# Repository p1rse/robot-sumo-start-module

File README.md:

Robot-sumo start module
=====================
Visit http://www.startmodule.com for information of how the start module system works.

This page is mainly for those who are interested in the sourcecode and schematics of the start module.

Purpose
====================
The purpose of this git repository is to maintain the robot-sumo start module system which is an open source and open hardware project.n
The purpose of the module is to make robot-sumo matches more fair and less time consuming by eliminating the possibilites of false starts.
This is done by each robot having a receiver(start module) that are programmed to suply the robot with at start signal when the referee sends the signal via an IR-remote.

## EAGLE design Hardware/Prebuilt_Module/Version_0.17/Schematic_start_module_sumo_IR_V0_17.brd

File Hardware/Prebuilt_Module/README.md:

Read me
=====================

The prebuilt modules are intended to be manufactured in larger quantities with pick and place machinery, this is to reduce size and cost.
The microcontroller on the prebuilt module has a very small amount of flash therefore the code is optimised for size and not so easy to understand.
If you have designed your own hardware and want to create code for this it is better to look at the code in the "Generic" folders.

Harware Version history
=====
Hardware version 0.16 is the version that was first sold at RobotChallenge 2012

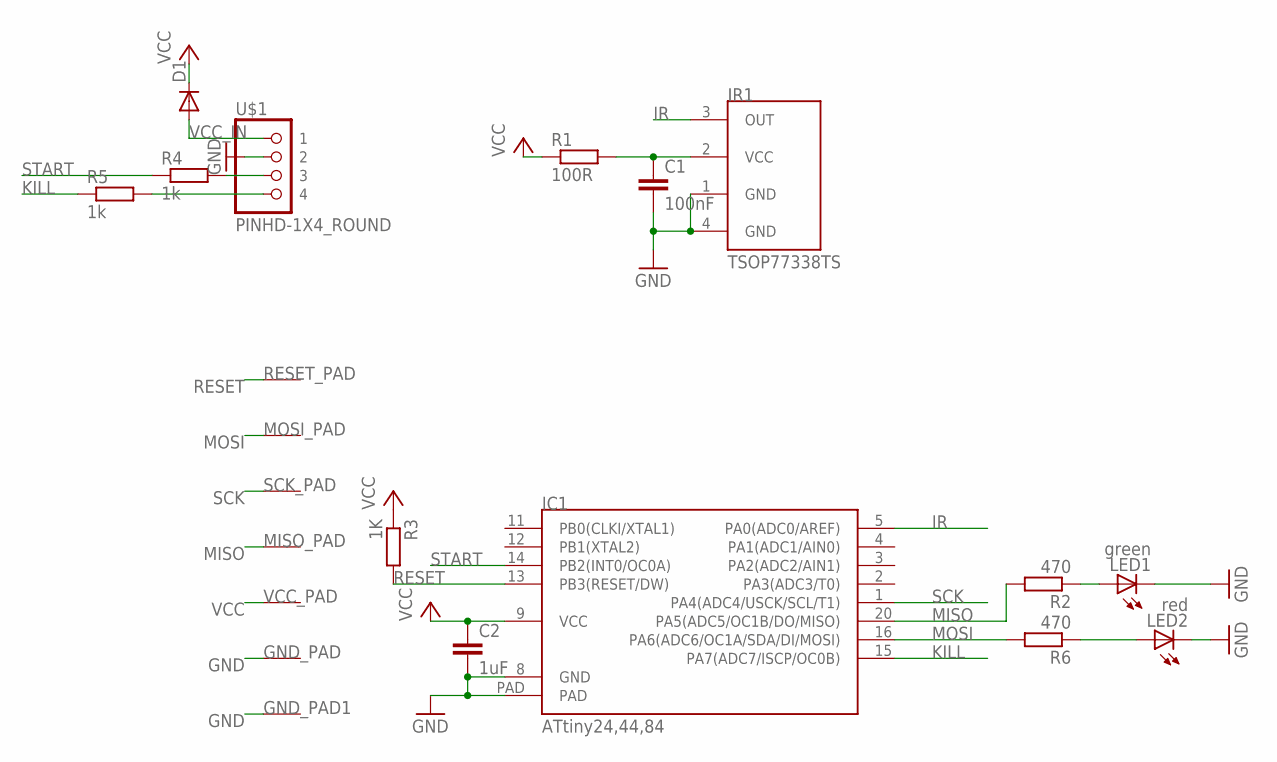
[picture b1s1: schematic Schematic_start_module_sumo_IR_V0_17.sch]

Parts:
C1: 100nF; C0603
C2: 1uF; C0603
D1: DIODE-SOD523; SOD523
GND_PAD: PAD50X50; PAD_50X50
GND_PAD1: PAD75X75; PAD_75X75
IC1: ATTINY24,44,84_QFNVQFN; VQFN20
IR1: TSOP77338TS; TSOP77338
LED1: green; 0603_SMALL
LED2: red; 0603_SMALL
MISO_PAD: PAD50X50; PAD_50X50
MOSI_PAD: PAD50X50; PAD_50X50
R1: 100R; R0402
R2, R6: 470; R0402
R3: 1K; R0402
R4, R5: 1k; R0402
RESET_PAD: PAD50X50; PAD_50X50
SCK_PAD: mosi; PAD_75X75
U$1: PINHD-1X4_ROUND; 1X04_ROUND
VCC_PAD: PAD50X50; PAD_50X50

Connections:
GND: C1.2, C2.2, GND_PAD.P$1, GND_PAD1.P$1, IC1.8 (GND), IC1.PAD, IR1.1 (GND), IR1.4 (GND), LED1.2 (C), LED2.2 (C), U$1.2
IR: IC1.5 (PA0(ADC0/AREF)), IR1.3 (OUT)
KILL: IC1.15 (PA7(ADC7/ISCP/OC0B)), R5.1
MISO: IC1.20 (PA5(ADC5/OC1B/DO/MISO)), MISO_PAD.P$1, R2.2
MOSI: IC1.16 (PA6(ADC6/OC1A/SDA/DI/MOSI)), MOSI_PAD.P$1, R6.2
unnamed: LED2.1 (A), R6.1
unnamed: C1.1, IR1.2 (VCC), R1.2
unnamed: LED1.1 (A), R2.1
unnamed: R5.2, U$1.4
unnamed: R4.2, U$1.3
RESET: IC1.13 (PB3(RESET/DW)), R3.2, RESET_PAD.P$1
SCK: IC1.1 (PA4(ADC4/USCK/SCL/T1)), SCK_PAD.P$1
START: IC1.14 (PB2(INT0/OC0A)), R4.1
VCC: C2.1, D1.C, IC1.9 (VCC), R1.1, R3.1, VCC_PAD.P$1
VCC_IN: D1.A, U$1.1

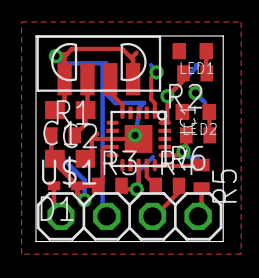
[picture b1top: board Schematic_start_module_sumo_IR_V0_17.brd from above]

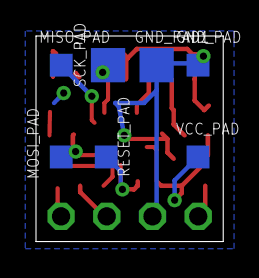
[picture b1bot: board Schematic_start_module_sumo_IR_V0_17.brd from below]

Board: 2 copper layers, 10.4 x 11.4 mm, 21 parts (7 on the bottom side), 15 nets.

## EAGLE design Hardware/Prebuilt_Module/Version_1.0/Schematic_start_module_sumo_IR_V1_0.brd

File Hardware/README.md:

Hardware
====================

Prebuilt_Module - this is the module built with pick and place machines.

Remote_Control - used by referees

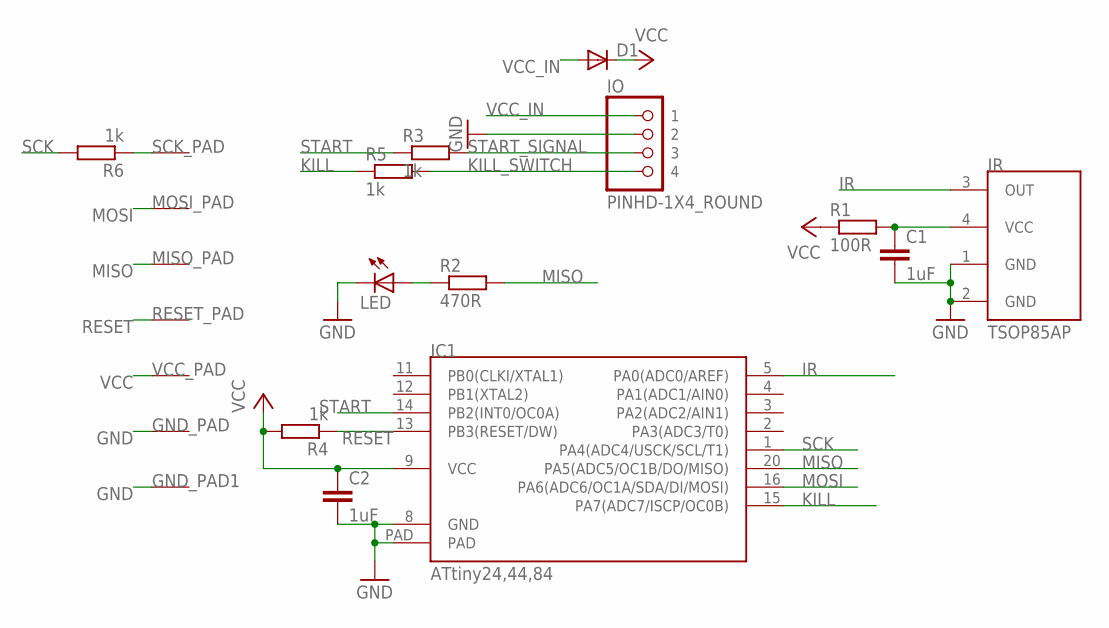
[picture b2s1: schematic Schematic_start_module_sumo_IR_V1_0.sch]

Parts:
C1, C2: 1uF; C0603
D1: DIODE-SOD523; SOD523
GND_PAD: PAD50X50; PAD_50X50
GND_PAD1: PAD75X75; PAD_75X75
IC1: ATTINY24,44,84_QFNVQFN; VQFN20
IO: PINHD-1X4_ROUND; 1X04_ROUND
IR: TSOP85AP
LED: LED0603; 0603_SMALL
MISO_PAD: mosi; PAD_50X50
MOSI_PAD: PAD50X50; PAD_50X50
R1: 100R; R0402
R2: 470R; R0402
R3, R4, R5, R6: 1k; R0402
RESET_PAD: PAD50X50; PAD_50X50
SCK_PAD: PAD75X75; PAD_75X75
VCC_PAD: PAD50X50; PAD_50X50

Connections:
GND: C1.2, C2.2, GND_PAD.P$1, GND_PAD1.P$1, IC1.8 (GND), IC1.PAD, IO.2, IR.1 (GND), IR.2 (GND), LED.2 (C)
IR: IC1.5 (PA0(ADC0/AREF)), IR.3 (OUT)
KILL: IC1.15 (PA7(ADC7/ISCP/OC0B)), R5.1
KILL_SWITCH: IO.4, R5.2
MISO: IC1.20 (PA5(ADC5/OC1B/DO/MISO)), MISO_PAD.P$1, R2.2
MOSI: IC1.16 (PA6(ADC6/OC1A/SDA/DI/MOSI)), MOSI_PAD.P$1
unnamed: LED.1 (A), R2.1
unnamed: R6.1, SCK_PAD.P$1
unnamed: C1.1, IR.4 (VCC), R1.2
RESET: IC1.13 (PB3(RESET/DW)), R4.1, RESET_PAD.P$1
SCK: IC1.1 (PA4(ADC4/USCK/SCL/T1)), R6.2
START: IC1.14 (PB2(INT0/OC0A)), R3.1
START_SIGNAL: IO.3, R3.2
VCC: C2.1, D1.C, IC1.9 (VCC), R1.1, R4.2, VCC_PAD.P$1
VCC_IN: D1.A, IO.1

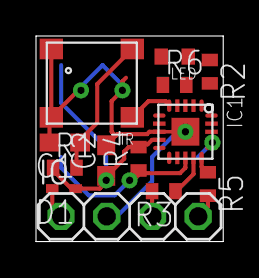
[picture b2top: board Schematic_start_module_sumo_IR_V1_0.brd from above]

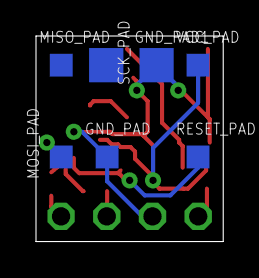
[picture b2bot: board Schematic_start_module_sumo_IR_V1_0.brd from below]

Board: 2 copper layers, 10.4 x 11.4 mm, 20 parts (7 on the bottom side), 15 nets.

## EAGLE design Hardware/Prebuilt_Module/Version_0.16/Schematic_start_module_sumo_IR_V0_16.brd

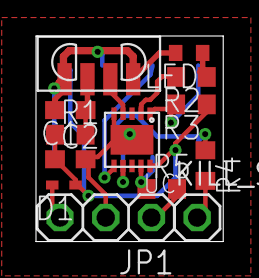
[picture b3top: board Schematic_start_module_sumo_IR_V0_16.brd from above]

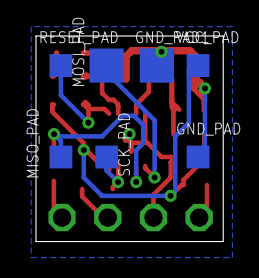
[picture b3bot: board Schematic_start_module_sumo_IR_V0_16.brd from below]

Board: 2 copper layers, 10.4 x 11.4 mm, 20 parts (7 on the bottom side), 13 nets.

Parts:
C1: 100nF; C0603
C2: 1uf; C0603
D1: SOD523
GND_PAD: PAD_50X50
GND_PAD1: PAD_75X75
IR1: TSOP77338TS; TSOP77338
JP1: 1X3
KILL_SWITCH: 1X01
LED: 0603_SMALL
MISO_PAD: PAD_50X50
MOSI_PAD: mosi; PAD_75X75
R1: 100Ohm; R0603
R2: 470; R0603
R3: 1K; R0603
R4, R5: 1KOhm; R0603
RESET_PAD: PAD_50X50
SCK_PAD: PAD_50X50
UC: ATTINY13A; DFN10
VCC_PAD: PAD_50X50

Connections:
GND: C1.2, C2.2, GND_PAD.P$1, GND_PAD1.P$1, IR1.1, IR1.4, JP1.2, LED.2, UC.5, UC.PAD
IR: IR1.3, UC.4
KILL_SWITCH: KILL_SWITCH.1, R4.2
MISO: MISO_PAD.P$1, R4.1, UC.7
MOSI: MOSI_PAD.P$1, UC.6
unnamed: R2.2, UC.2
unnamed: LED.1, R2.1
unnamed: C1.1, IR1.2, R1.2
RESET: R3.2, RESET_PAD.P$1, UC.1
SCK: R5.1, SCK_PAD.P$1, UC.9
START_SIGNAL: JP1.1, R5.2
VCC: C2.1, D1.C, R1.1, R3.1, UC.10, VCC_PAD.P$1
VCC_IN: D1.A, JP1.3

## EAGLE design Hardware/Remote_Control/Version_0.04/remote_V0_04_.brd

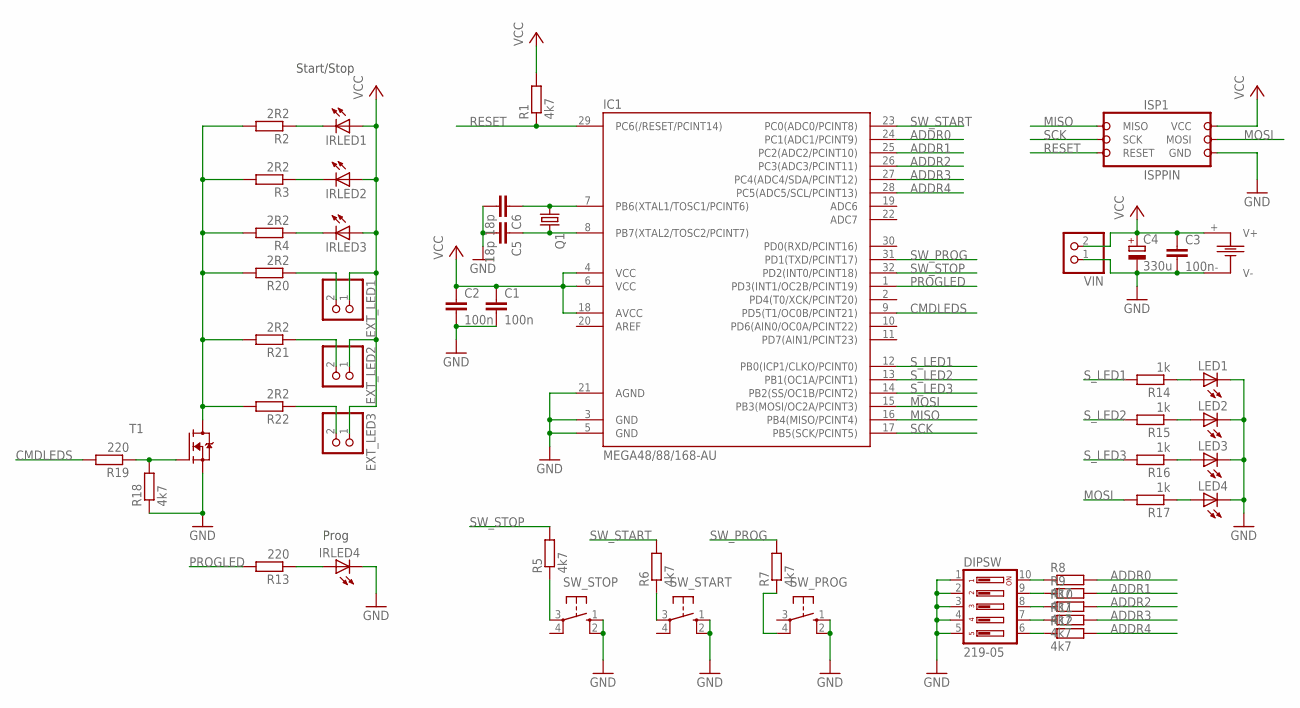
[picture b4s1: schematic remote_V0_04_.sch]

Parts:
B1: BATTERY_HOLDER_1; BAT_HOLDER_1
C1, C2, C3: 100n; C0805WP
C4: 330u; SANYO-OSCON_SMD_C6
C5, C6: 18p; C0805WP
DIPSW: 219-05; CTS-219-05
EXT_LED1, EXT_LED2, EXT_LED3: PINHD-1X2LONG; 1X2LONG
IC1: MEGA48/88/168-AU; TQFP32-08
IRLED1, IRLED2, IRLED3, IRLED4: LEDLED5MMH; LED5MMH
ISP1: ISPPIN; 2X03
LED1, LED2, LED3, LED4: LED0805; LED_0805
Q1: CRYSTALHC49S; HC49/S
R1, R5, R6, R7, R8, R9, R10, R11, R12, R18: 4k7; R0805WP
R2, R3, R4, R20, R21, R22: 2R2; R0805WP
R13, R19: 220; R0805WP
R14, R15, R16, R17: 1k; R0805WP
SW_PROG: 10-XX; B3F-10XX
SW_START: 10-XX; B3F-10XX
SW_STOP: 10-XX; B3F-10XX
T1: MOSFET_N_SOT23; SOT23
VIN: PINHD-1X2; 1X02

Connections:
ADDR0: IC1.24 (PC1(ADC1/PCINT9)), R8.2
ADDR1: IC1.25 (PC2(ADC2/PCINT10)), R9.2
ADDR2: IC1.26 (PC3(ADC3/PCINT11)), R10.2
ADDR3: IC1.27 (PC4(ADC4/SDA/PCINT12)), R11.2
ADDR4: IC1.28 (PC5(ADC5/SCL/PCINT13)), R12.2
CMDLEDS: IC1.9 (PD5(T1/OC0B/PCINT21)), R19.2
GND: B1.- (V-), C1.2, C2.2, C3.2, C4.-, C5.2, C6.2, DIPSW.1, DIPSW.2, DIPSW.3, DIPSW.4, DIPSW.5, IC1.3 (GND), IC1.5 (GND), IC1.21 (AGND), IRLED4.P$2 (C), ISP1.6 (GND), LED1.C, LED2.C, LED3.C, LED4.C, R18.1, SW_PROG.1 (S), SW_PROG.2 (S1), SW_START.1 (S), SW_START.2 (S1), SW_STOP.1 (S), SW_STOP.2 (S1), T1.2 (S), VIN.1
MISO: IC1.16 (PB4(MISO/PCINT4)), ISP1.1 (MISO)
MOSI: IC1.15 (PB3(MOSI/OC2A/PCINT3)), ISP1.4 (MOSI), R17.2
unnamed: IRLED1.P$2 (C), R2.1
unnamed: IRLED2.P$2 (C), R3.1
unnamed: IRLED3.P$2 (C), R4.1
unnamed: DIPSW.10, R8.1
unnamed: DIPSW.9, R9.1
unnamed: DIPSW.8, R10.1
unnamed: DIPSW.7, R11.1
unnamed: DIPSW.6, R12.1
unnamed: R5.1, SW_STOP.3
unnamed: R6.1, SW_START.3
unnamed: R7.1, SW_PROG.4 (P1)
unnamed: IRLED4.P$1 (A), R13.1
unnamed: R18.2, R19.1, T1.1 (G)
unnamed: LED1.A, R14.1
unnamed: LED2.A, R15.1
unnamed: LED3.A, R16.1
unnamed: LED4.A, R17.1
unnamed: C6.1, IC1.7 (PB6(XTAL1/TOSC1/PCINT6)), Q1.1
unnamed: EXT_LED1.2, R20.1
unnamed: EXT_LED2.2, R21.1
unnamed: R2.2, R3.2, R4.2, R20.2, R21.2, R22.2, T1.3 (D)
unnamed: EXT_LED3.2, R22.1
unnamed: C5.1, IC1.8 (PB7(XTAL2/TOSC2/PCINT7)), Q1.2
PROGLED: IC1.1 (PD3(INT1/OC2B/PCINT19)), R13.2
RESET: IC1.29 (PC6(/RESET/PCINT14)), ISP1.5 (RESET), R1.1
SCK: IC1.17 (PB5(SCK/PCINT5)), ISP1.3 (SCK)
SW_PROG: IC1.31 (PD1(TXD/PCINT17)), R7.2
SW_START: IC1.23 (PC0(ADC0/PCINT8)), R6.2
SW_STOP: IC1.32 (PD2(INT0/PCINT18)), R5.2
S_LED1: IC1.12 (PB0(ICP1/CLKO/PCINT0)), R14.2
S_LED2: IC1.13 (PB1(OC1A/PCINT1)), R15.2
S_LED3: IC1.14 (PB2(SS/OC1B/PCINT2)), R16.2
VCC: B1.+ (V+), C1.1, C2.1, C3.1, C4.+, EXT_LED1.1, EXT_LED2.1, EXT_LED3.1, IC1.4 (VCC), IC1.6 (VCC), IC1.18 (AVCC), IRLED1.P$1 (A), IRLED2.P$1 (A), IRLED3.P$1 (A), ISP1.2 (VCC), R1.2, VIN.2

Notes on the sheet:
Start/Stop
Prog

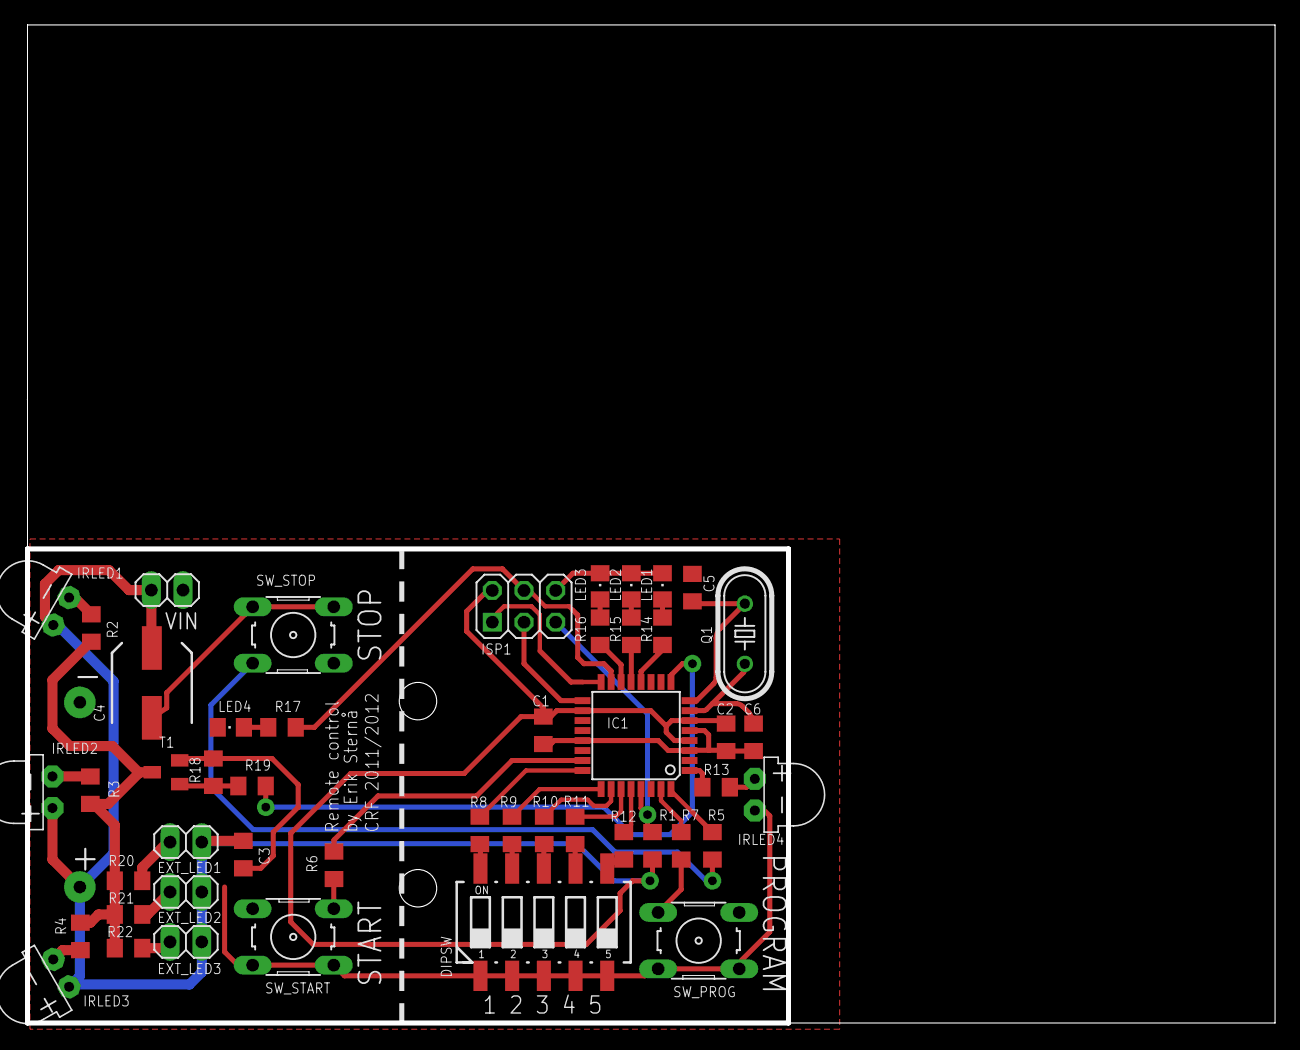
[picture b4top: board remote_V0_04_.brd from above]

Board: 2 copper layers, 99.8 x 79.8 mm, 49 parts (1 on the bottom side), 42 nets.

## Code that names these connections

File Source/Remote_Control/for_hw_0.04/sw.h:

/*
 * sw.h
 *
 *  Created on: 16 jan 2012
 *      Author: Sterna
 */

#ifndef SW_H_
#define SW_H_

#include <avr/io.h>

/*
 * I use internal pullups on all switches, thus receiving logical 0 at button press
 */

#define SW_PROG (!(PIND & _BV(1)))
#define SW_STOP (!(PIND & _BV(2)))
#define SW_START (!(PINC & _BV(0)))
#define SW_DIP (~(PINC>>1) & 0b00011111)

void initSW();

unsigned char readDip();

#endif /* SW_H_ */

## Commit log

2012-09-08 First commit testing file structure
2012-09-08 testing folder struture
2012-09-08 added files that previoulsy was on the homepage
2012-09-08 gitignore for emac backup files
2012-09-08 rename folder and updating som read me files
2012-09-09 uploaded hex files and some comments in main.c for remote control
2012-09-09 Drill sizes for battery holder updated
    Drill sizes for the holes on the battery holder were to small. Changed
    from 0.8 mm to 1.0 mm.
    Also added some files to .gitignore.
2012-09-09 Added component lists in open office format
2012-10-17 Repetition updated
    Updated the software of the remote control. Updated 2 things:
    - Start and stop commands are sent as while button is held, thus making
    it easier to stop the robots
    - Set the repetition frequency to 114ms, which is standard for RC5. It
    can be set in main.h
2012-10-17 Produced new gerber files
2012-11-24 New branch
    Created a new branch to use as development for the new updtated
    version of the start module.
2012-11-24 Board-test
    Github did not want me to sync withput commiting this change...
2012-11-24 New hardware design for start module
    Performed changes:
    - Redesign of board
    - Changed the microcontroller from Attiny13A to Attiny24/44A
    - Changed the ir-receiver from TSOP75x to TSOP85x_AP5
    Resons for these changes are mainly the following two points:
    - 1. The IR-receiver used in the previous version was hard to get ahold
2012-11-25 Some corrections from 1.0
    Due to some errors, I decided to switch to 0402 components, thus making
    it easier to route and to add another feature: a serial resistor for
    the home-pad. The signals for the pads used for the pogo-bead are
    changed. The positions are still the same, but the signals are a little
    mixed.
2012-11-25 Updated components in component list
2012-12-08 Version 0.17
    Since it was not very expensive to get the manufacturer to flip the
    IR-receiver, it's best to go with a version similar to the old one
    (V0.16). What is new from that verison is a new microcontroller
    (Attiny44A), anothe LED and resistors in 0402.
    Furthermore, the version with another IR-receiver (V1.0) has been
    slightly updated.
2013-01-17 Changed repetition frequency (again)
    Changed how the start commands are sent. using the last revisions code,
    a situation could happen where one robot starts a long time after the
    other, which would lead to an unfair match. This update makes the start
    button send start commands very quickly. Stop commands are still sent
    at a rate of 114ms as long as stop button is pressed.
2013-02-24 Description of fusebits for ATtiny13A
    Added a guide on how to set the program the chip when used the
    precompiled program if you build your own module using an ATtiny13A
    (check the Readme at Source/Prebuilt_Module).
2013-03-27 Changed repetition frequency (again) Changed how the start commands are sent. using the last revisions code, a situation could happen where one robot starts a long time after the other, which would l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
2019-10-02 Update README.md
    Uppdated URL to official startmodule page since it was outdated
2019-10-04 Added makefiles to compile and flash to target as well as README files
2019-10-10 Fixed a bug in the upload startmodule code command Added command to upload the remote control code.
2019-10-11 Renamed hex file to include FW version and which HW version they are built for FW 1.0 are the current version that was already in the repo
2019-11-27 Verified fix for discharge bug in Referee remote as identified and proposed by Drykov. Verified that current in stand-by(after pressing a button) before bug fix was 0.21mA and after the bugfix 0.01mA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
2019-12-01 Added new hex file with fix for discharge bug (see previous commit)
2022-05-20 Update Makefile
    Corrected the clock speed as proposed by Eryk-Mozdzen.
